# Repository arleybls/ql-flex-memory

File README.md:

# QL Flex Memory Expansion

A 512kB external RAM expansion for the Sinclair QL, based on Alvaro Alea
Fernandez's design. The circuit is unchanged. This version reworks the board to
make assembly and reconfiguration easier, hence the name.

Original project: https://github.com/alvaroalea/QL_512kb_External_Expansion

## Changes in the 2025 revision

* Standard 2.54mm pin headers replace the configuration solder jumpers. Jumper
  caps now control the memory configuration and Trump Card mode.
* The GAL16V8 uses a PLCC-20 SMD socket instead of a DIP-20 through-hole package.
  The GAL remains removable and reprogrammable while taking up less board space.
* The resistors and 100nF capacitors use the 0805 size instead of 1206.
* The silkscreen includes the memory configuration table
  (00-512kB / 01-256kB / 10-192kB / 11-128kB), NORMAL/TRUMP labels for the mode
  header, and the board dimensions.
* All fabrication outputs are in one `gerbers/` folder.

Board size (97.79 × 35.56 mm) and the circuit itself are unchanged from the
original rev 3.

## About the board

The board adds up to 512kB of static RAM (fast RAM) to the Sinclair QL.

Stacking two boards provides up to 896kB of memory, the same capacity as
Miracle's Trump Card.

Two memory expansions cannot occupy the same address range. This applies to
Jose Leandro's QBide, the Trump Card, and similar hardware.

The board has an expansion connector for additional interfaces.

The configuration headers provide four settings. The original board uses solder
jumpers instead.

* 512kB: The standard expansion for any QL.
* 256kB: Used as a second expansion to reach the QL's 896kB maximum. This setting
  conflicts with many expansion cards. Any card without configuration jumpers
  will be incompatible.
* 192kB: Similar to the 256kB setting, but leaves more address space for properly
  configured expansion cards.
* 128kB: Similar to the 256kB setting, with still more address space left for
  properly configured expansion cards.

The 128kB configuration cannot be installed alone. To use it for a total of
768kB, another expansion card must provide ROM at address E00000h. Without that
ROM, an overlap between the internal and external 128kB causes the QL ROM to
report a RAM malfunction and hang.

https://www.instagram.com/p/CZWfWcUM5mx/

The `gal` folder contains source code for GALasm:
https://github.com/daveho/GALasm

## RAM test software

`software/memtest/` contains a RAM test for checking an assembled card on the QL.
It combines a SuperBASIC front end with a 68008 machine-code core. The suite
tests the data bus, address bus, aliasing (GAL decode), March C-minus, and
checkerboard patterns. It supports a QDOS-safe mode and a destructive test of
the complete window. See
[software/memtest/README.md](software/memtest/README.md).

## Mini Trump Card compatibility

Alvaro also made the MiniTrump version of the Trump Card disk interface:
https://github.com/alvaroalea/QL_MiniTrump3. Unlike the original, the MiniTrump
does not include memory. Combining it with two of these RAM cards provides the
same functions as the original Trump Card.

Connect the 512kB card to the QL, the MiniTrump to the 512kB card, and the +256kB
card to the MiniTrump. Set this board's three-pin mode header, labelled
NORMAL/TRUMP on the silkscreen, to TRUMP so the MiniTrump can coordinate with
the second memory card.

## Credits and license

Original design (C) 2022 Alvaro Alea Fernandez, based on the work of McLeod
Ideafix, Jose Leandro, Zerover and tcat among others, with contributions from
www.va-de-retro.com

2025 revisions by ArleyJr.

Licensed under: CERN Open Hardware Licence Version 2 - Strongly Reciprocal

https://ohwr.org/cern_ohl_s_v2.txt

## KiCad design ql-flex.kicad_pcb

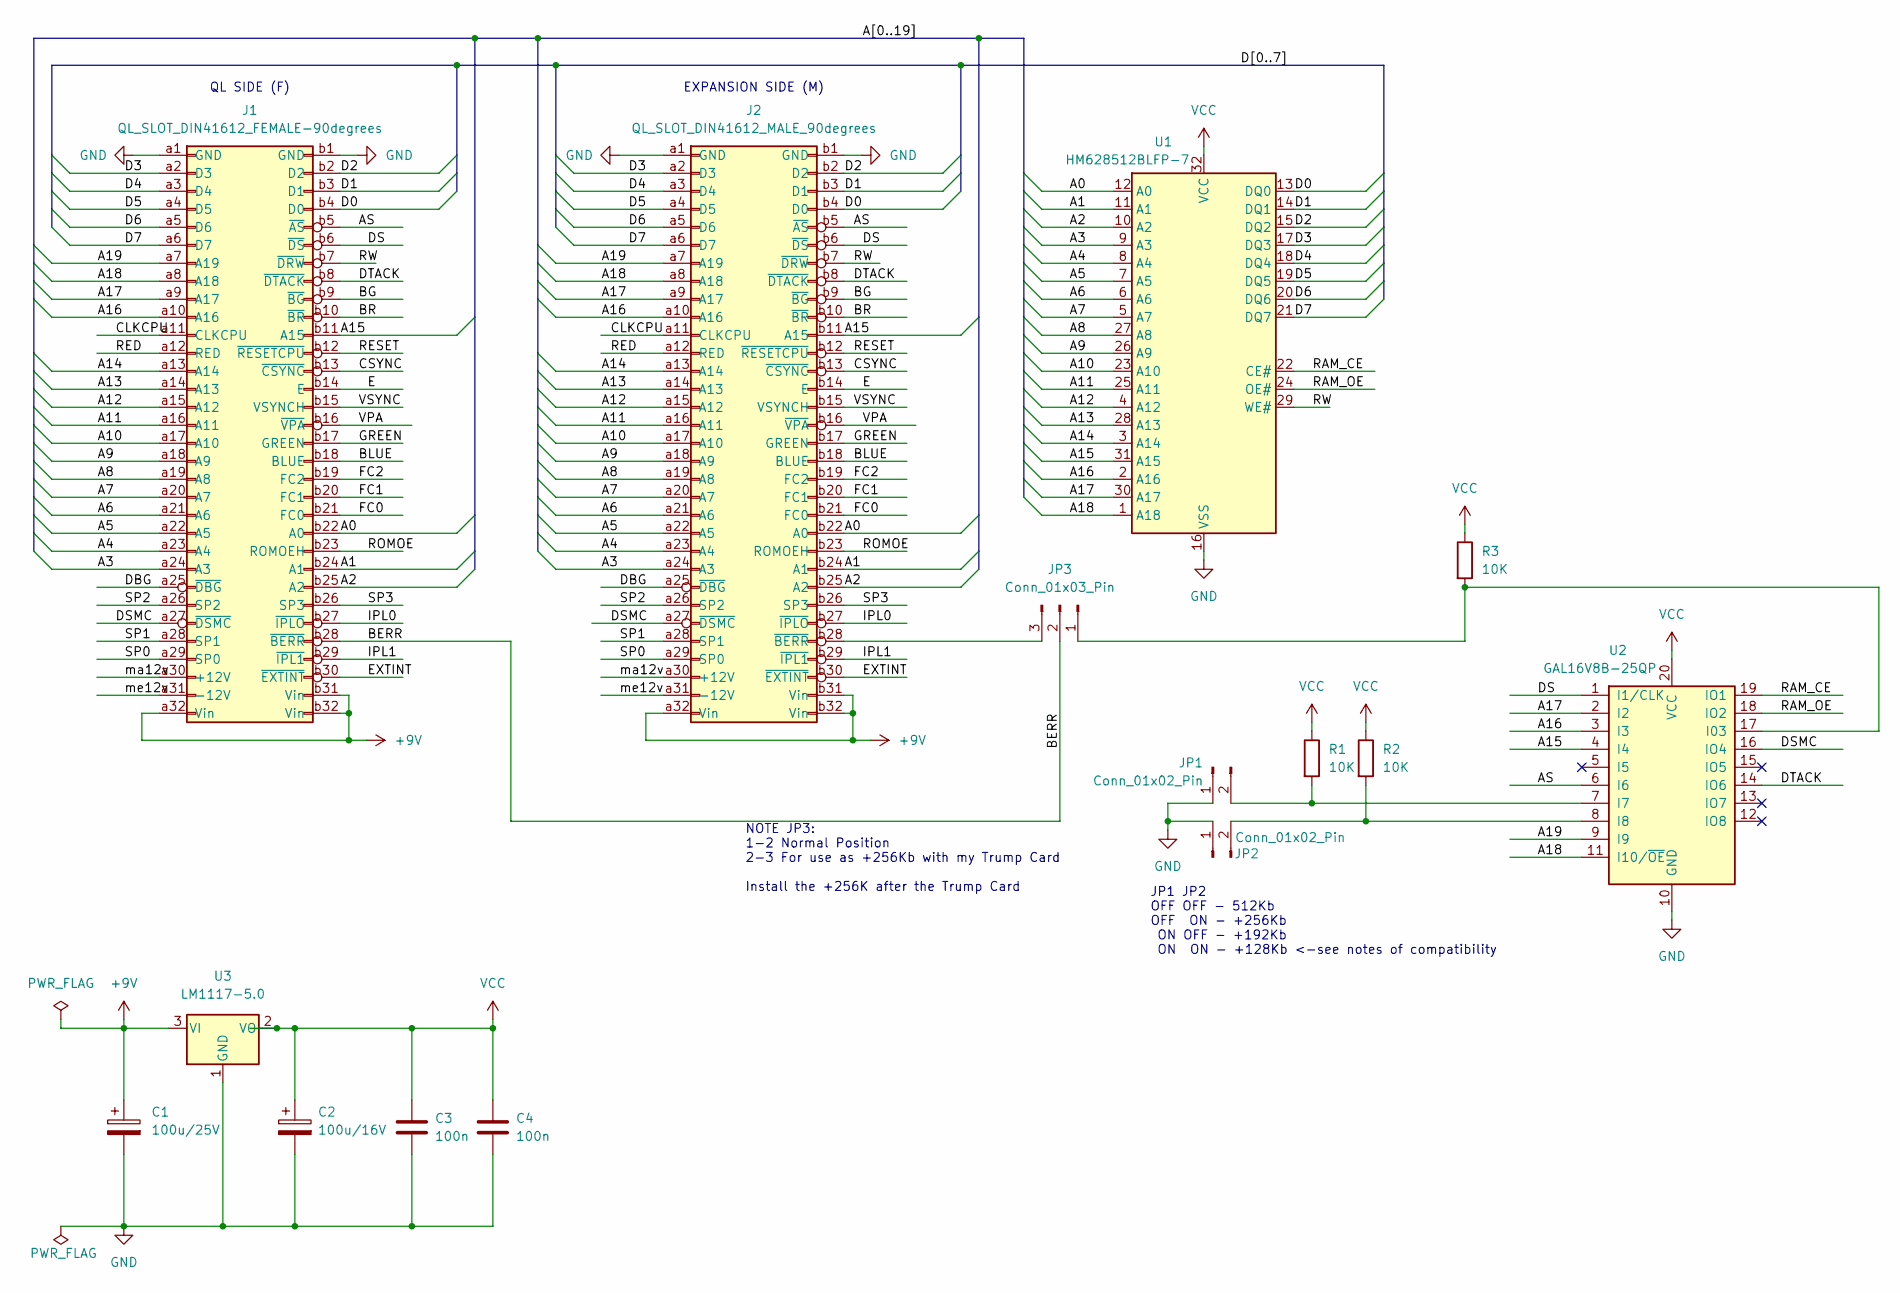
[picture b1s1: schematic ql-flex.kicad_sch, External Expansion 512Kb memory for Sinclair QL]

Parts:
C1: 100u/25V; CP_Elec_6.3x5.4
C2: 100u/16V; CP_Elec_6.3x5.4
C3, C4: 100n; C_0805_2012Metric_Pad1.18x1.45mm_HandSolder
J1: QL_SLOT_DIN41612_FEMALE-90degrees; DIN41612_B_2x32_Female_Horizontal_THT
J2: QL_SLOT_DIN41612_MALE_90degrees; DIN41612_B_2x32_Male_Horizontal_THT
JP1, JP2: Conn_01x02_Pin; PinHeader_1x02_P2.54mm_Vertical
JP3: Conn_01x03_Pin; PinHeader_1x03_P2.54mm_Vertical
R1, R2, R3: 10K; R_0805_2012Metric_Pad1.20x1.40mm_HandSolder
U1: HM628512BLFP-7; SSOP-32_11.305x20.495mm_P1.27mm
U2: GAL16V8B-25QP; PLCC-20_SMD-Socket
U3: LM1117-5.0; SOT-223-3_TabPin2

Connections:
+9V: C1.1, J1.a32 (Vin), J1.b31 (Vin), J1.b32 (Vin), J2.a32 (Vin), J2.b31 (Vin), J2.b32 (Vin), U3.3 (VI)
/A0: J1.b22 (A0), J2.b22 (A0), U1.12 (A0)
/A1: J1.b24 (A1), J2.b24 (A1), U1.11 (A1)
/A2: J1.b25 (A2), J2.b25 (A2), U1.10 (A2)
/A3: J1.a24 (A3), J2.a24 (A3), U1.9 (A3)
/A4: J1.a23 (A4), J2.a23 (A4), U1.8 (A4)
/A5: J1.a22 (A5), J2.a22 (A5), U1.7 (A5)
/A6: J1.a21 (A6), J2.a21 (A6), U1.6 (A6)
/A7: J1.a20 (A7), J2.a20 (A7), U1.5 (A7)
/A8: J1.a19 (A8), J2.a19 (A8), U1.27 (A8)
/A9: J1.a18 (A9), J2.a18 (A9), U1.26 (A9)
/A10: J1.a17 (A10), J2.a17 (A10), U1.23 (A10)
/A11: J1.a16 (A11), J2.a16 (A11), U1.25 (A11)
/A12: J1.a15 (A12), J2.a15 (A12), U1.4 (A12)
/A13: J1.a14 (A13), J2.a14 (A13), U1.28 (A13)
/A14: J1.a13 (A14), J2.a13 (A14), U1.3 (A14)
/A15: J1.b11 (A15), J2.b11 (A15), U1.31 (A15), U2.4 (I4)
/A16: J1.a10 (A16), J2.a10 (A16), U1.2 (A16), U2.3 (I3)
/A17: J1.a9 (A17), J2.a9 (A17), U1.30 (A17), U2.2 (I2)
/A18: J1.a8 (A18), J2.a8 (A18), U1.1 (A18), U2.11 (I10/~OE)
/A19: J1.a7 (A19), J2.a7 (A19), U2.9 (I9)
/AS: J1.b5 (~AS), J2.b5 (~AS), U2.6 (I6)
/BERR: J1.b28 (~BERR), JP3.2
/BG: J1.b9 (~BG), J2.b9 (~BG)
/BLUE: J1.b18 (BLUE), J2.b18 (BLUE)
/BR: J1.b10 (~BR), J2.b10 (~BR)
/CLKCPU: J1.a11 (CLKCPU), J2.a11 (CLKCPU)
/CSYNC: J1.b13 (~CSYNC), J2.b13 (~CSYNC)
/D0: J1.b4 (D0), J2.b4 (D0), U1.13 (DQ0)
/D1: J1.b3 (D1), J2.b3 (D1), U1.14 (DQ1)
/D2: J1.b2 (D2), J2.b2 (D2), U1.15 (DQ2)
/D3: J1.a2 (D3), J2.a2 (D3), U1.17 (DQ3)
/D4: J1.a3 (D4), J2.a3 (D4), U1.18 (DQ4)
/D5: J1.a4 (D5), J2.a4 (D5), U1.19 (DQ5)
/D6: J1.a5 (D6), J2.a5 (D6), U1.20 (DQ6)
/D7: J1.a6 (D7), J2.a6 (D7), U1.21 (DQ7)
/DBG: J1.a25 (~DBG), J2.a25 (~DBG)
/DS: J1.b6 (~DS), J2.b6 (~DS), U2.1 (I1/CLK)
/DSMC: J1.a27 (~DSMC), J2.a27 (~DSMC), U2.16 (IO4)
/DTACK: J1.b8 (~DTACK), J2.b8 (~DTACK), U2.14 (IO6)
/E: J1.b14 (E), J2.b14 (E)
/EXTINT: J1.b30 (~EXTINT), J2.b30 (~EXTINT)
/FC0: J1.b21 (FC0), J2.b21 (FC0)
/FC1: J1.b20 (FC1), J2.b20 (FC1)
/FC2: J1.b19 (FC2), J2.b19 (FC2)
/GREEN: J1.b17 (GREEN), J2.b17 (GREEN)
/IPL0: J1.b27 (~IPLO), J2.b27 (~IPLO)
/IPL1: J1.b29 (~IPL1), J2.b29 (~IPL1)
/RAM_CE: U1.22 (CE#), U2.19 (IO1)
/RAM_OE: U1.24 (OE#), U2.18 (IO2)
/RED: J1.a12 (RED), J2.a12 (RED)
/RESET: J1.b12 (~RESETCPU), J2.b12 (~RESETCPU)
/ROMOE: J1.b23 (ROMOEH), J2.b23 (ROMOEH)
/RW: J1.b7 (~DRW), J2.b7 (~DRW), U1.29 (WE#)
/SP0: J1.a29 (SP0), J2.a29 (SP0)
/SP1: J1.a28 (SP1), J2.a28 (SP1)
/SP2: J1.a26 (SP2), J2.a26 (SP2)
/SP3: J1.b26 (SP3), J2.b26 (SP3)
/VPA: J1.b16 (~VPA), J2.b16 (~VPA)
/VSYNC: J1.b15 (VSYNCH), J2.b15 (VSYNCH)
/ma12v: J1.a30 (+12V), J2.a30 (+12V)
/me12v: J1.a31 (-12V), J2.a31 (-12V)
GND: C1.2, C2.2, C3.2, C4.2, J1.a1 (GND), J1.b1 (GND), J2.a1 (GND), J2.b1 (GND), JP1.1, JP2.1, U1.16 (VSS), U2.10 (GND), U3.1 (GND)
unnamed: J2.b28 (~BERR), JP3.3
unnamed: JP1.2, R1.2, U2.7 (I7)
unnamed: JP2.2, R2.2, U2.8 (I8)
unnamed: JP3.1, R3.2, U2.17 (I03)
VCC: C2.1, C3.1, C4.1, R1.1, R2.1, R3.1, U1.32 (VCC), U2.20 (VCC), U3.2 (VO)

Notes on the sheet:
NOTE JP3: 1-2 Normal Position 2-3 For use as +256Kb with my Trump Card Install the +256K after the Trump Card
EXPANSION SIDE (M)
JP1 JP2 OFF OFF - 512Kb OFF ON - +256Kb ON OFF - +192Kb ON ON - +128Kb <-see notes of compatibility
QL SIDE (F)

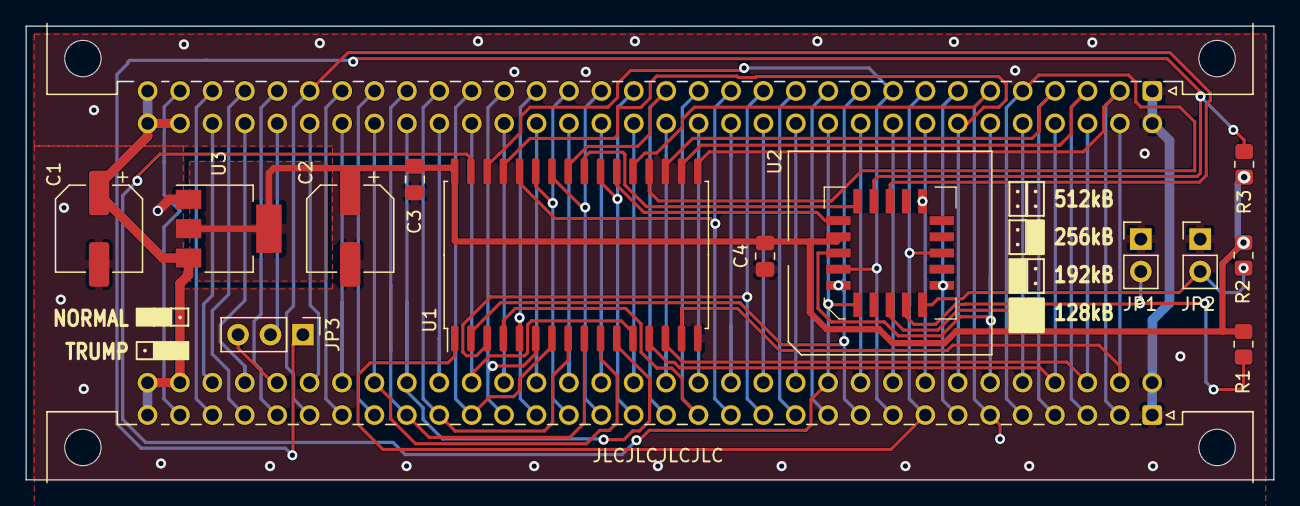
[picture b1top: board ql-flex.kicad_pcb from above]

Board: 2 copper layers, 97.8 x 35.6 mm, 15 parts (0 on the bottom side), 68 nets.

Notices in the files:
ql-flex.kicad_pcb:
(C) 2022 Alvaro Alea Fdz.
Under License
(C) 2022-2024 By Alvaro Alea Fdz.
Licensed under Cern OHL-S
